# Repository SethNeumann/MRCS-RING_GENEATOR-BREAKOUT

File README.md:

# REPO NAME: MRCS-RING_GENERATOR-BREAKOUT
## License: Creative Commons Attribution-NonCommercial-ShareAlike

Board for potted ring generator module. Mounts in 70mm Tyco Track (MD) inputs power (screw term and barrel jack), output, straps to select frequency,
optionally add pads for other varieties. The modules are long since MD and data sheets are not available for the PCR-SIN01=V12F00A which I bought oneBay
some suppliers claim to have them.

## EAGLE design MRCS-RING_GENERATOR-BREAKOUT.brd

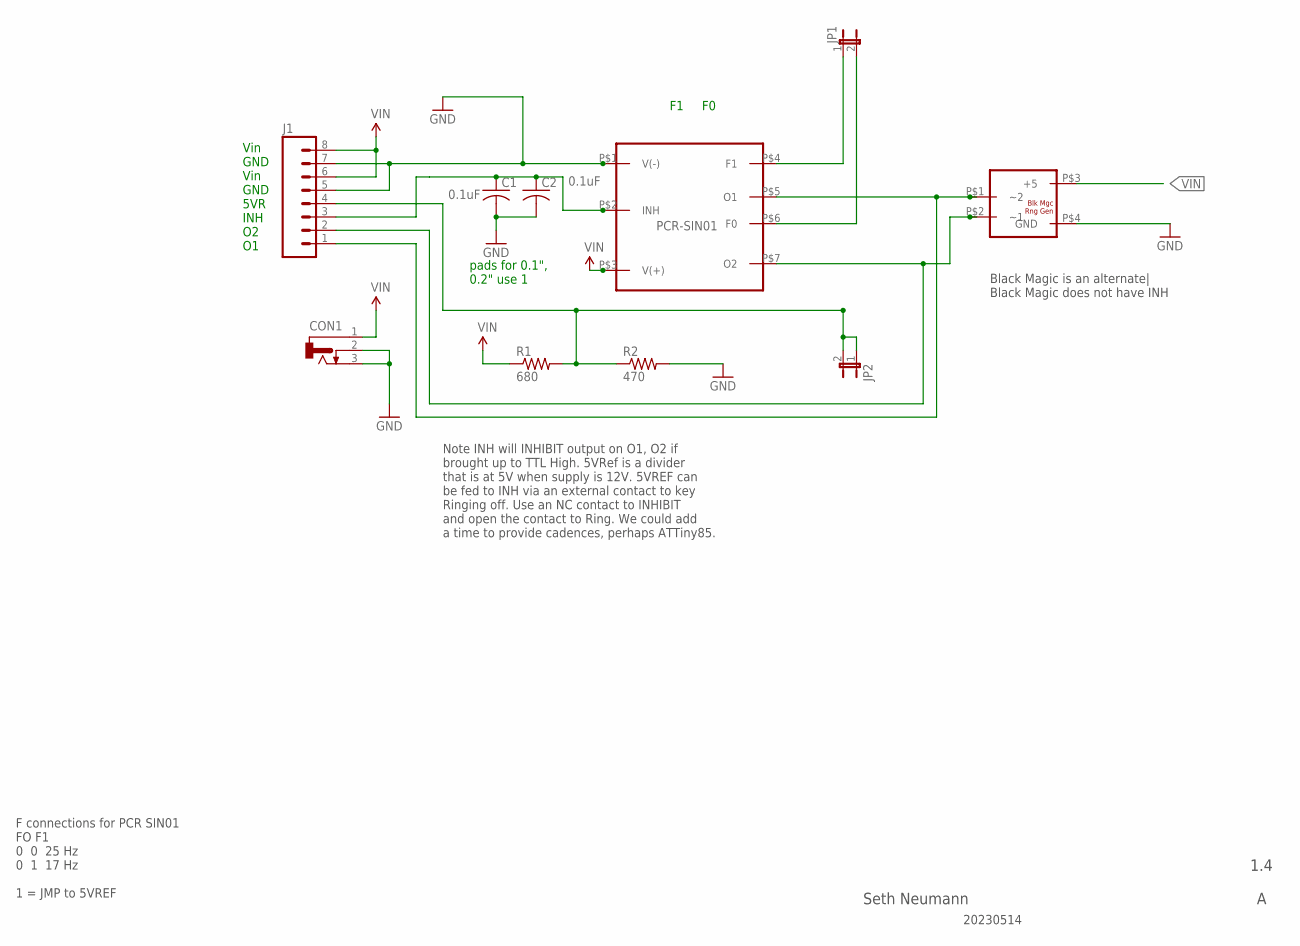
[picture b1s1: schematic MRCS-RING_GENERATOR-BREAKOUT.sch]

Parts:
C1: 0.1uF; C050-024X044
C2: 0.1uF; C-PTH-0.100
CON1: CONNECTOR-DC-POWER-RA; DCJ0202
J1: CONNECTOR-M08LOCK; 1X08_LOCK
JP1, JP2: JUMPER-2PTH_LOCK; 1X02_LOCK
R1: 680; AXIAL-0.4-RES
R2: 470; AXIAL-0.4-RES
U$1: PCR-SIN01
U$5: BLACK_MAGIC_RING_GEN

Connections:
5VREF: J1.4, JP2.1, JP2.2, R1.P$2 (2), R2.P$1 (1)
F0: JP1.2, U$1.P$6 (F0)
F1: JP1.1, U$1.P$4 (F1)
GND: C1.2, C2.2, CON1.2, CON1.3, J1.5, J1.7, R2.P$2 (2), U$1.P$1 (V(-)), U$5.P$4 (GND)
INH: C1.1, C2.1, J1.3, U$1.P$2 (INH)
O1: J1.1, U$1.P$5 (O1), U$5.P$1 (~2)
O2: J1.2, U$1.P$7 (O2), U$5.P$2 (~1)
VIN: CON1.1, J1.6, J1.8, R1.P$1 (1), U$1.P$3 (V(+)), U$5.P$3 (+5)

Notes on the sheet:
1.4
Seth Neumann
F connections for PCR SIN01 FO F1 0 0 25 Hz 0 1 17 Hz 1 = JMP to 5VREF
F1 F0
pads for 0.1", 0.2" use 1
Vin GND Vin GND 5VR INH O2 O1
Note INH will INHIBIT output on O1, O2 if brought up to TTL High. 5VRef is a divider that is at 5V when supply is 12V. 5VREF can be fed to INH via an external contact to key Ringing off. Use an NC contact to INHIBIT and open the contact to Ring. We could add a time to provide cadences, perhaps ATTi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
Black Magic is an alternate| Black Magic does not have INH
20230514

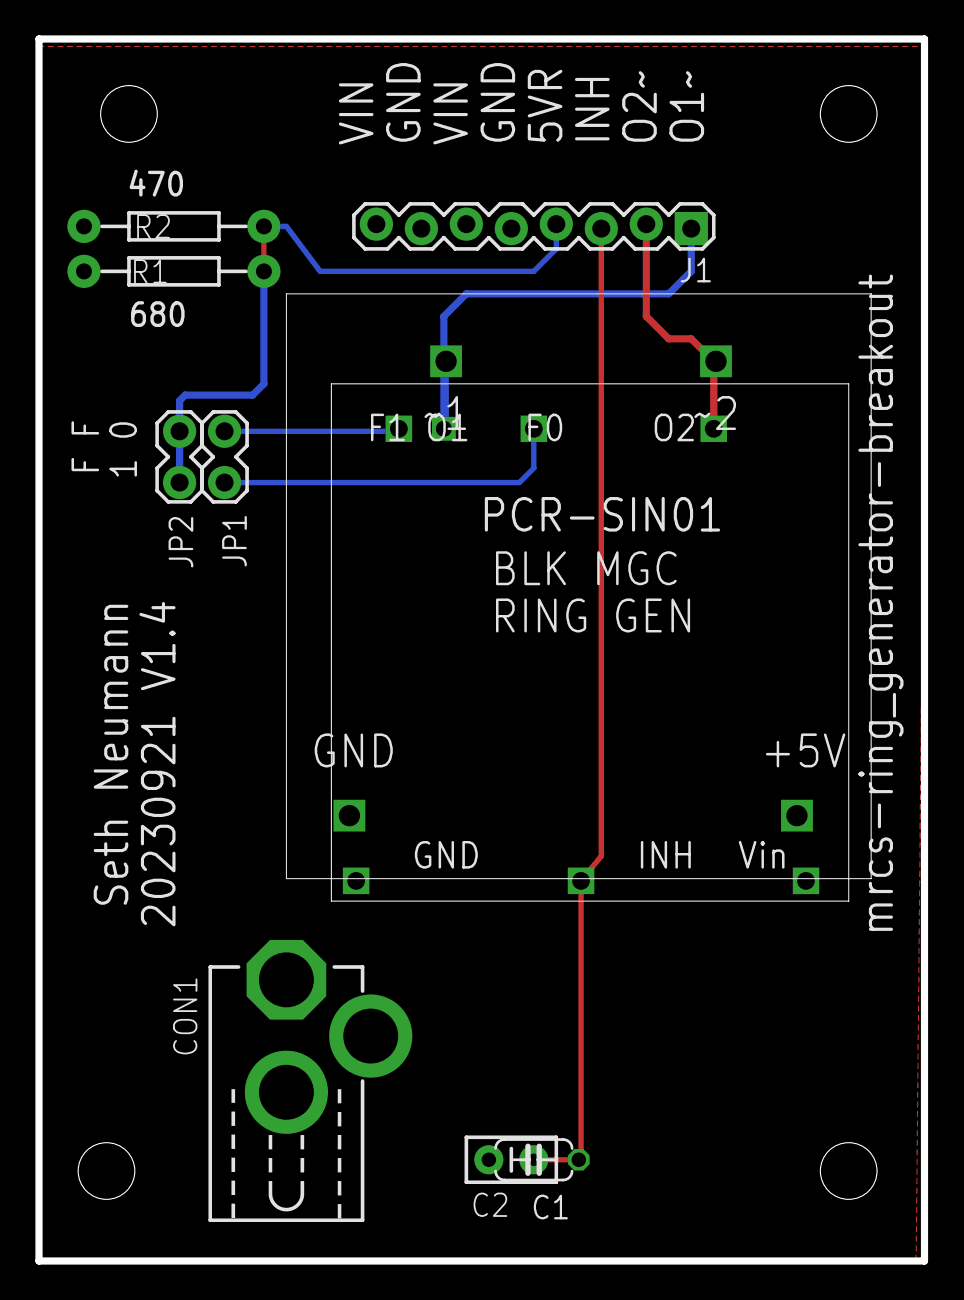
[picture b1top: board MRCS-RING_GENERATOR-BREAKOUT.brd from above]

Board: 2 copper layers, 50.0 x 69.0 mm, 13 parts (0 on the bottom side), 8 nets.

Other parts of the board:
U$2: MRCSLOGOTOP
U$3: CA-PROP65WARNING
U$4: MRCSLOGOBTM

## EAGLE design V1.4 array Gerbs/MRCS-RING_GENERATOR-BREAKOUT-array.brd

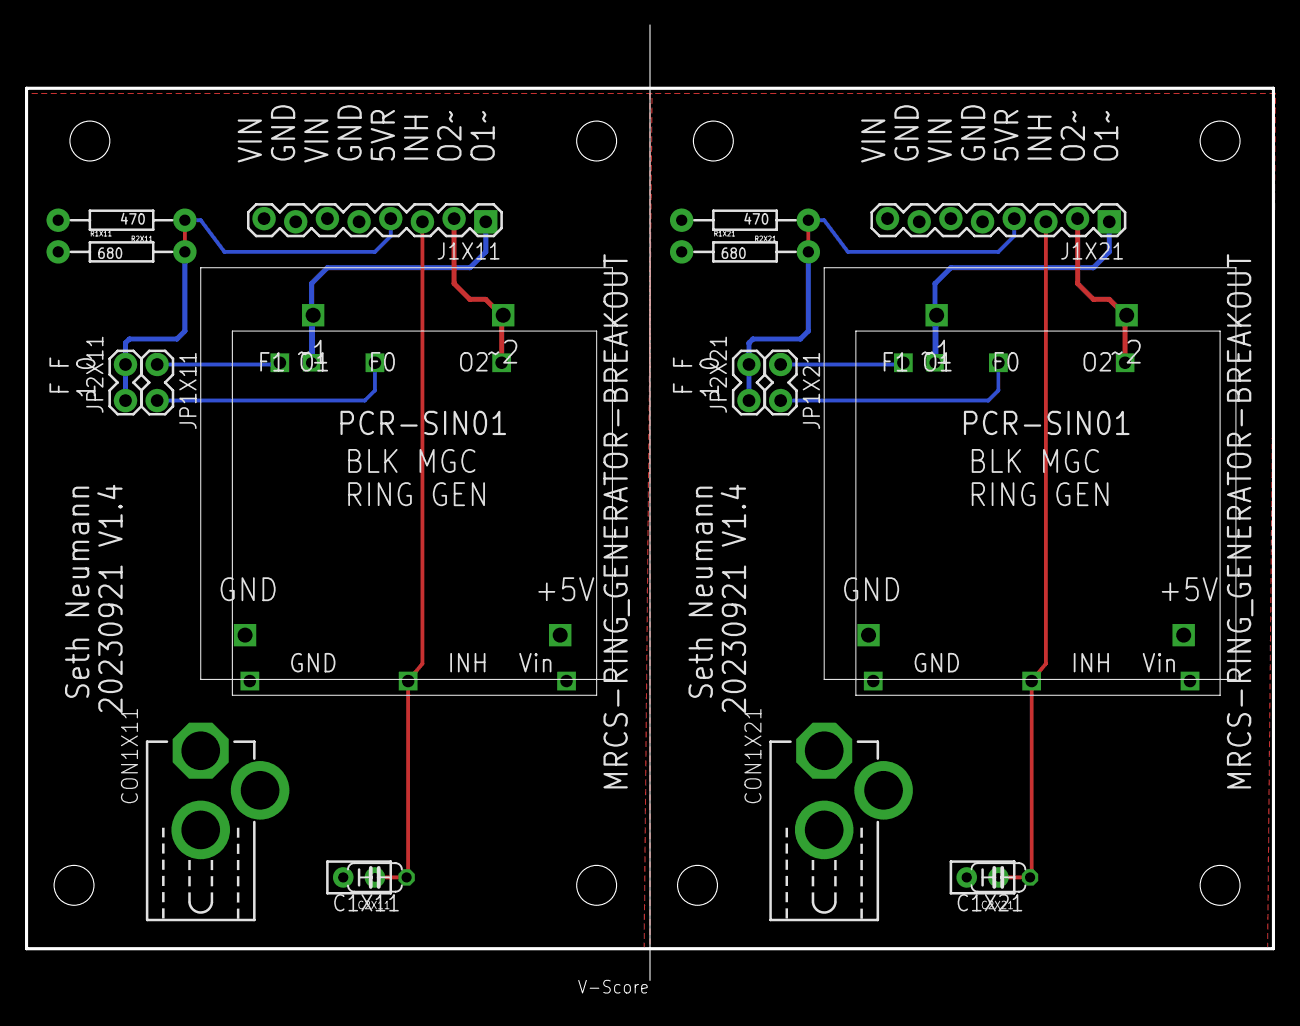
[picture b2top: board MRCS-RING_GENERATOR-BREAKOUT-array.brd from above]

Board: 2 copper layers, 100.0 x 78.0 mm, 26 parts (0 on the bottom side), 16 nets.

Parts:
C1X11, C1X21: 0.1uF; C050-024X044
C2X11, C2X21: 0.1uF; C-PTH-0.100
CON1X11, CON1X21: DCJ0202
J1X11, J1X21: 1X08_LOCK
JP1X11, JP1X21, JP2X11, JP2X21: 1X02_LOCK
R1X11, R1X21: 680; AXIAL-0.4-RES
R2X11, R2X21: 470; AXIAL-0.4-RES
U$1X11, U$1X21: PCR-SIN01
U$2X11, U$2X21: MRCSLOGOTOP
U$3X11, U$3X21: CA-PROP65WARNING
U$4X11, U$4X21: MRCSLOGOBTM
U$5X11, U$5X21: BLACK_MAGIC_RING_GEN

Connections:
5VREFX11: J1X11.4, JP2X11.1, JP2X11.2, R1X11.P$2, R2X11.P$1
5VREFX21: J1X21.4, JP2X21.1, JP2X21.2, R1X21.P$2, R2X21.P$1
F0X11: JP1X11.2, U$1X11.P$6
F0X21: JP1X21.2, U$1X21.P$6
F1X11: JP1X11.1, U$1X11.P$4
F1X21: JP1X21.1, U$1X21.P$4
GNDX11: C1X11.2, C2X11.2, CON1X11.2, CON1X11.3, J1X11.5, J1X11.7, R2X11.P$2, U$1X11.P$1, U$5X11.P$4
GNDX21: C1X21.2, C2X21.2, CON1X21.2, CON1X21.3, J1X21.5, J1X21.7, R2X21.P$2, U$1X21.P$1, U$5X21.P$4
INHX11: C1X11.1, C2X11.1, J1X11.3, U$1X11.P$2
INHX21: C1X21.1, C2X21.1, J1X21.3, U$1X21.P$2
O1X11: J1X11.1, U$1X11.P$5, U$5X11.P$1
O1X21: J1X21.1, U$1X21.P$5, U$5X21.P$1
O2X11: J1X11.2, U$1X11.P$7, U$5X11.P$2
O2X21: J1X21.2, U$1X21.P$7, U$5X21.P$2
VINX11: CON1X11.1, J1X11.6, J1X11.8, R1X11.P$1, U$1X11.P$3, U$5X11.P$3
VINX21: CON1X21.1, J1X21.6, J1X21.8, R1X21.P$1, U$1X21.P$3, U$5X21.P$3

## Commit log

2023-05-11 corrected spelling
2023-05-11 creating working directory
2023-09-17 Version 1.3 updates
2023-09-17 Update DESCRIPTION
2023-09-17 Update INFO
    reflect V1.3 productions status
2023-09-17 Various updates while preparing documentation
2023-09-17 Create Ringing Generator Breakout Assembly and Installation Instructions V0_1.pdf
    First Pass documentation
2023-09-17 Delete V1.1 Gerbs directory
    obsolete
2023-09-17 clean up after product page on website
    clean up after product page on website
2023-10-07 panelized 2 up version
2023-10-07 Updated Assembly and Installation Instructions
    Installation and test info

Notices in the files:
parts and their libraries:
SparkFun-Aesthetics: Licensing: CC v3.0 Share-Alike You are welcome to use this library for commercial purposes.
